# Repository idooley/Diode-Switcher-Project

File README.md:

# A Clipping Diode Selection Circuit
## _Do different clipping diodes matter in a Guitar Distortion/Overdrive circuit?_

This repo contains a rudimentary circuit board design that allows selection among 12 pairs of symmetric clipping diodes. The project was created in KiCad 6, and files are available here for anyone who wants to use them in their own projects.

Note, I have not yet assembled a working device from this design. 

## Why?
This circuit makes it easier to test various types of diodes in a Guitar Distortion Pedal. If this board is connected in place of the regular clipping diodes, it should be easy to rotate the switch and select among various alternatives.

## Features
- Designed for [this 12-way rotary switch](https://www.digikey.com/en/products/detail/e-switch/KC10A9-501NPS/1804492) based on its [drawings](https://spec_sheets.e-switch.com/specs/G527521.pdf). 
- Provides spaces for 12 pairs of diodes (or other components), with one end of each pair grounded, and the other end attached to one position on the switch.
- Gerber files and Drill files have been generated for anyone who wants to order their own PCBs from the cheap JLCPCB manufacturer. You might be able to get 10 boards there for $5 + shipping. If you prefer another manufacturer, you can generate appropriate gerbers from the KiCad project files also included in this repo.

## License

CERN Open Hardware Licence Version 2 - Permissive

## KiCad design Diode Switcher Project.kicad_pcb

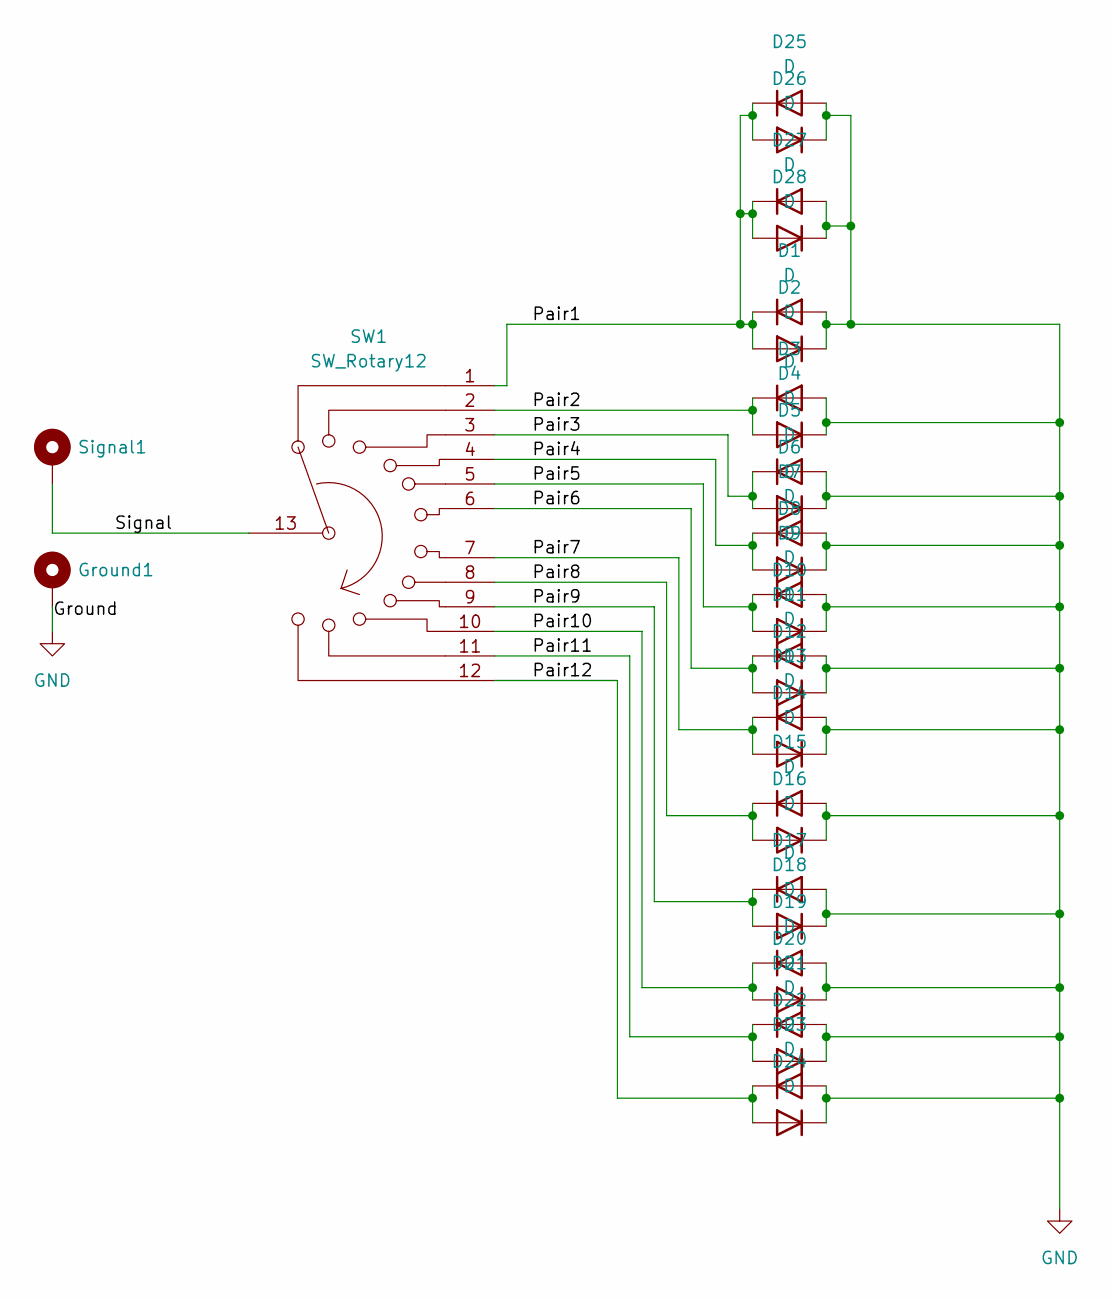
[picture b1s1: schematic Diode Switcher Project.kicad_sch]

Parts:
D1, D2, D3, D4, D5, D6, D7, D8, D9, D10, D11, D12, D13, D14, D15, D16, D17, D18, D19, D20, D21, D22, D23, D24: D; D_DO-15_P15.24mm_Horizontal
D25, D26: D; D_DO-15_P2.54mm_Vertical_AnodeUp
D27, D28: D; D_DO-15_P5.08mm_Vertical_AnodeUp
Ground1: MountingHole_Pad; SolderWire-0.75sqmm_1x01_D1.25mm_OD2.3mm
SW1: SW_Rotary12; Rotary Switch KC10A9.501NPS
Signal1: MountingHole_Pad; SolderWire-0.75sqmm_1x01_D1.25mm_OD2.3mm

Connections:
/Pair1: D1.1 (K), D2.2 (A), D25.1 (K), D26.2 (A), D27.1 (K), D28.2 (A), SW1.1
/Pair2: D3.1 (K), D4.2 (A), SW1.2
/Pair3: D5.1 (K), D6.2 (A), SW1.3
/Pair4: D7.1 (K), D8.2 (A), SW1.4
/Pair5: D9.1 (K), D10.2 (A), SW1.5
/Pair6: D11.1 (K), D12.2 (A), SW1.6
/Pair7: D13.1 (K), D14.2 (A), SW1.7
/Pair8: D15.1 (K), D16.2 (A), SW1.8
/Pair9: D17.1 (K), D18.2 (A), SW1.9
/Pair10: D19.1 (K), D20.2 (A), SW1.10
/Pair11: D21.1 (K), D22.2 (A), SW1.11
/Pair12: D23.1 (K), D24.2 (A), SW1.12
/Signal: SW1.13, Signal1.1
GND: D1.2 (A), D2.1 (K), D3.2 (A), D4.1 (K), D5.2 (A), D6.1 (K), D7.2 (A), D8.1 (K), D9.2 (A), D10.1 (K), D11.2 (A), D12.1 (K), D13.2 (A), D14.1 (K), D15.2 (A), D16.1 (K), D17.2 (A), D18.1 (K), D19.2 (A), D20.1 (K), D21.2 (A), D22.1 (K), D23.2 (A), D24.1 (K), D25.2 (A), D26.1 (K), D27.2 (A), D28.1 (K), Ground1.1

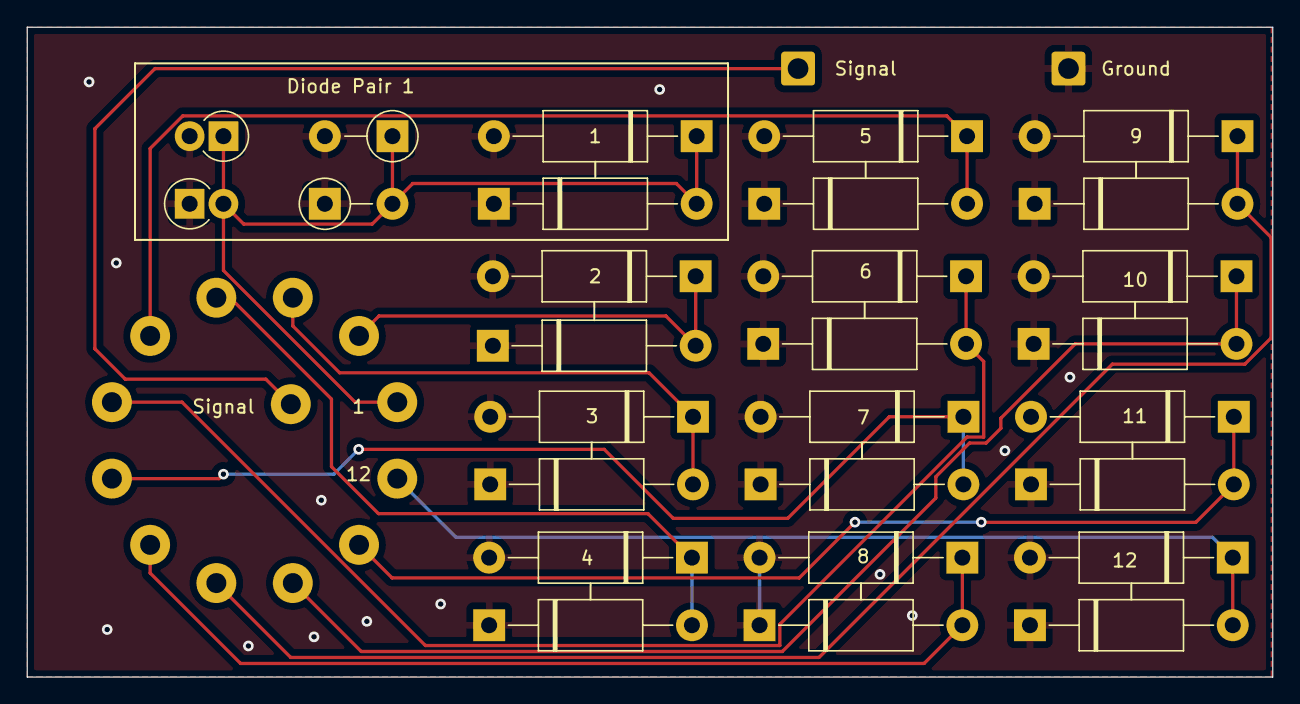
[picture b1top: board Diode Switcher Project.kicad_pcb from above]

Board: 2 copper layers, 93.6 x 48.8 mm, 31 parts (1 on the bottom side), 14 nets.

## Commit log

2022-06-18 Initial KiCad 6 project files and Gerbers and Drill Files for JLCPCB
2022-06-18 Add README
